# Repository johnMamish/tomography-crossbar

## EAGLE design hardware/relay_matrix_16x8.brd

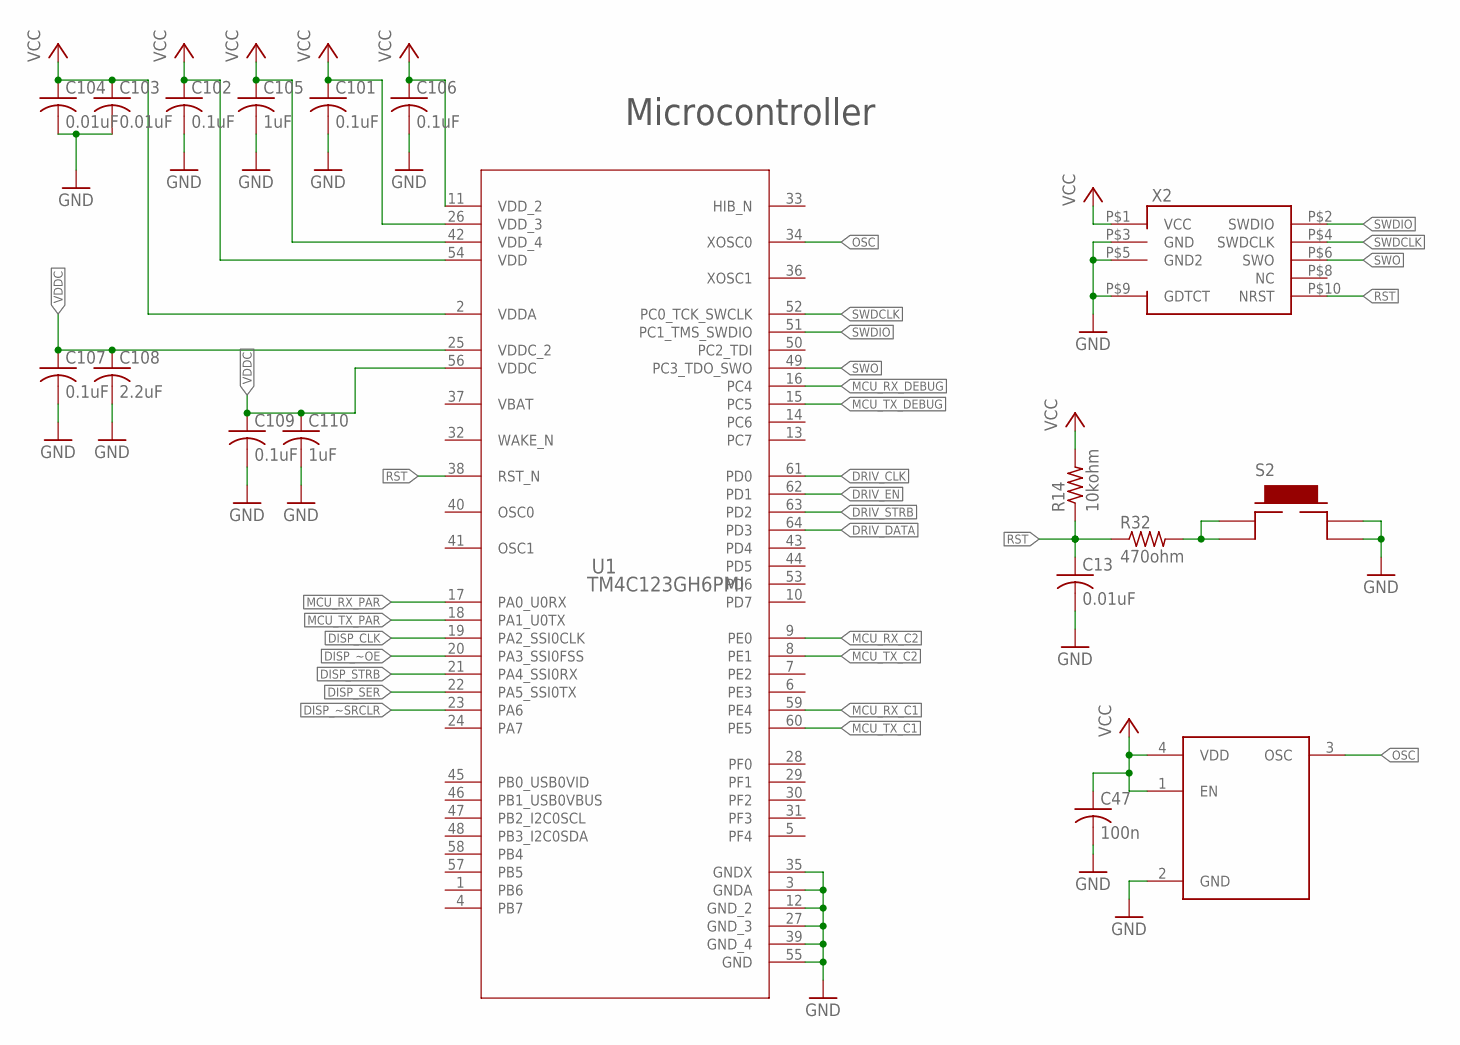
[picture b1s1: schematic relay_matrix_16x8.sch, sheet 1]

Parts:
C13, C103, C104: 0.01uF; C0402; MANUFACTURER_PART_NUMBER GCM155R71H103KA55D
C47: 100n; C0402; MANUFACTURER_PART_NUMBER CL05B104KO5NNNC
C101, C102, C106, C107, C109: 0.1uF; C0402; MANUFACTURER_PART_NUMBER CL05B104KO5NNNC
C105, C110: 1uF; C0402; MANUFACTURER_PART_NUMBER CL05A105KO5NNNC
C108: 2.2uF; C0603; MANUFACTURER_PART_NUMBER CL10A225KO8NNNC
R14: 10kohm; R0402; MANUFACTURER_PART_NUMBER RC1005F103CS
R32: 470ohm; R0402; MANUFACTURER_PART_NUMBER RC0402JR-07470RL
S2: TE_FSM4JSMA; TE_FSMJSMA; MANUFACTURER_PART_NUMBER FSM4JSMA
U1: TM4C123GH6PMI; PM0064A_N
U5: ECS-2033-080-AU; OSCCC250X200X110N; MANUFACTURER_PART_NUMBER ECS-2033-080-AU
X2: FTSH-105-01-F-DV-007-K-P; MANUFACTURER_PART_NUMBER FTSH-105-01-F-DV-007-K-P

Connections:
!RST: C13.1, R14.1, R32.1, U1.38 (RST_N), X2.P$10 (NRST)
DISP_CLK: U1.19 (PA2_SSI0CLK); also elsewhere on the board
DISP_SER: U1.22 (PA5_SSI0TX); also elsewhere on the board
DISP_STRB: U1.21 (PA4_SSI0RX); also elsewhere on the board
DISP_~OE: U1.20 (PA3_SSI0FSS); also elsewhere on the board
DISP_~SRCLR: U1.23 (PA6); also elsewhere on the board
DRIV_CLK: U1.61 (PD0); also elsewhere on the board
DRIV_DATA: U1.64 (PD3); also elsewhere on the board
DRIV_EN: U1.62 (PD1); also elsewhere on the board
DRIV_STRB: U1.63 (PD2); also elsewhere on the board
GND: C13.2, C47.2, C101.2, C102.2, C103.2, C104.2, C105.2, C106.2, C107.2, C108.2, C109.2, C110.2, S2.P$3, S2.P$4, U1.3 (GNDA), U1.12 (GND_2), U1.27 (GND_3), U1.35 (GNDX), U1.39 (GND_4), U1.55 (GND), U5.2 (GND), X2.P$3 (GND), X2.P$5 (GND2), X2.P$9 (GDTCT); also elsewhere on the board
MCU_RX_C1: U1.59 (PE4); also elsewhere on the board
MCU_RX_C2: U1.9 (PE0); also elsewhere on the board
MCU_RX_DEBUG: U1.16 (PC4); also elsewhere on the board
MCU_RX_PAR: U1.17 (PA0_U0RX); also elsewhere on the board
MCU_TX_C1: U1.60 (PE5); also elsewhere on the board
MCU_TX_C2: U1.8 (PE1); also elsewhere on the board
MCU_TX_DEBUG: U1.15 (PC5); also elsewhere on the board
MCU_TX_PAR: U1.18 (PA1_U0TX); also elsewhere on the board
unnamed: R32.2, S2.P$1, S2.P$2
OSC: U1.34 (XOSC0), U5.3 (OSC)
SWDCLK: U1.52 (PC0_TCK_SWCLK), X2.P$4 (SWDCLK)
SWDIO: U1.51 (PC1_TMS_SWDIO), X2.P$2 (SWDIO)
SWO: U1.49 (PC3_TDO_SWO), X2.P$6 (SWO)
VBAT: U1.37 (VBAT)
VCC: C47.1, C101.1, C102.1, C103.1, C104.1, C105.1, C106.1, R14.2, U1.2 (VDDA), U1.11 (VDD_2), U1.26 (VDD_3), U1.42 (VDD_4), U1.54 (VDD), U5.1 (EN), U5.4 (VDD), X2.P$1 (VCC); also elsewhere on the board
VDDC: C107.1, C108.1, C109.1, C110.1, U1.25 (VDDC_2), U1.56 (VDDC)

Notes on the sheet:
Microcontroller

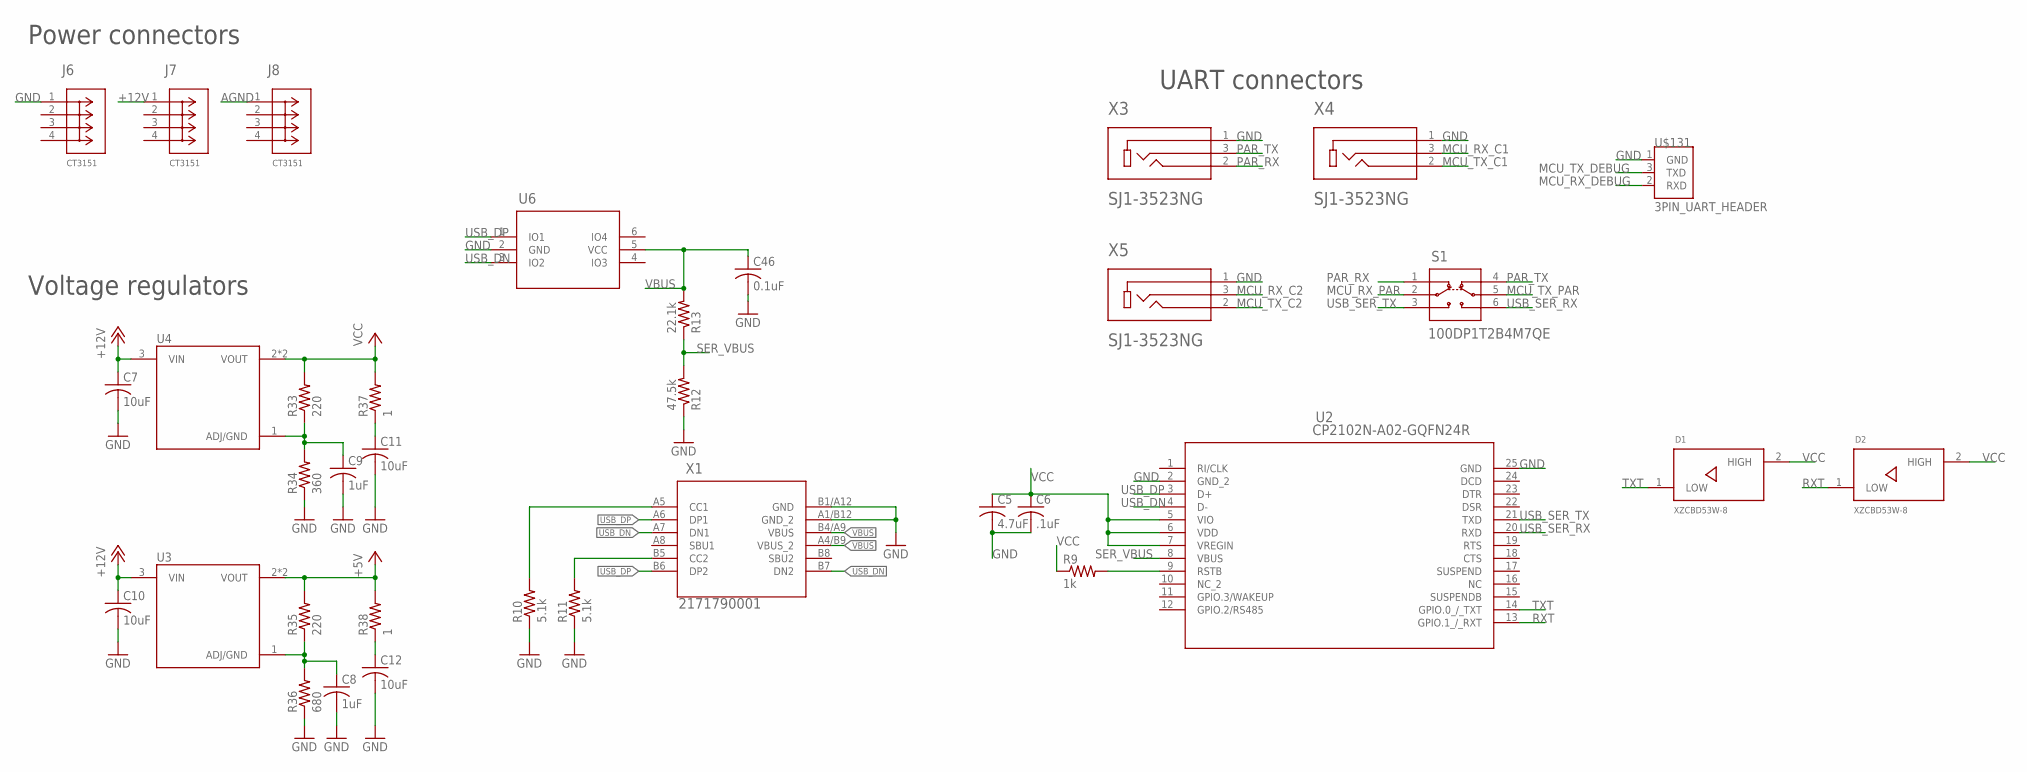
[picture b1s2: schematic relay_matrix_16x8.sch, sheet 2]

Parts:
C5: 4.7uF; C0603; MANUFACTURER_PART_NUMBER CL10A475KA8NQNC
C6: .1uF; C0402; MANUFACTURER_PART_NUMBER CL05A105KO5NNNC
C7, C10, C11, C12: 10uF; C0805; MANUFACTURER_PART_NUMBER CL21A106KAYNNNE
C8, C9: 1uF; C0402; MANUFACTURER_PART_NUMBER CL05A105KO5NNNC
C46: 0.1uF; C0402; MANUFACTURER_PART_NUMBER CL05B104KO5NNNC
D1, D2: XZCBD53W-8; DIOC1608X70N
J6, J7, J8: CT3151; CONN_CT3151
R9: 1k; R0402; MANUFACTURER_PART_NUMBER CRG0402F1K0
R10, R11: 5.1k; R0402; MANUFACTURER_PART_NUMBER RC0402FR-075K1L
R12: 47.5k; R0402; MANUFACTURER_PART_NUMBER RMCF0402FT47K5
R13: 22.1k; R0402; MANUFACTURER_PART_NUMBER RC0402FR-0722K1L
R33, R35: 220; R0603; MANUFACTURER_PART_NUMBER RC1608F221CS
R34: 360; R0603; MANUFACTURER_PART_NUMBER RC0603FR-07360RL
R36: 680; R0603; MANUFACTURER_PART_NUMBER RC0603FR-07680RL
R37, R38: 1; R0603; MANUFACTURER_PART_NUMBER RC0603FR-071RL
S1: 100DP1T2B4M7QE; 100DP1T2B4M7QE_EWI
U2: CP2102N-A02-GQFN24R; QFN24_SIL
U3, U4: NCP1117XXA; TO230P990X240-4N; MANUFACTURER_PART_NUMBER NCP1117IDTAT4G
U6: TPD4E001RDBVR; DBV6
U$131: 3PIN_UART_HEADER; HDRV3W64P254_1X3_1016X277X854B
X1: 2171790001; 2171790001_MOL
X3, X4, X5: SJ1-3523NG; CUI_SJ1-3523NG; MANUFACTURER_PART_NUMBER SJ1-3523NG

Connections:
+5V: R35.2, R38.2, U3.2 (VOUT), U3.4 (VOUT); also elsewhere on the board
+12V: C7.1, C10.1, J7.1, U3.3 (VIN), U4.3 (VIN)
AGND: J8.1; also elsewhere on the board
GND: C5.2, C6.2, C7.2, C8.2, C9.2, C10.2, C11.2, C12.2, C46.2, J6.1, R10.1, R11.1, R12.1, R34.1, R36.1, U2.2 (GND_2), U2.25 (GND), U6.2 (GND), U$131.1 (GND), X1.A1/B12 (GND_2), X1.B1/A12 (GND), X3.1, X4.1, X5.1; also elsewhere on the board
MCU_RX_C1: X4.3; also elsewhere on the board
MCU_RX_C2: X5.3; also elsewhere on the board
MCU_RX_DEBUG: U$131.2 (RXD); also elsewhere on the board
MCU_RX_PAR: S1.2; also elsewhere on the board
MCU_TX_C1: X4.2; also elsewhere on the board
MCU_TX_C2: X5.2; also elsewhere on the board
MCU_TX_DEBUG: U$131.3 (TXD); also elsewhere on the board
MCU_TX_PAR: S1.5; also elsewhere on the board
unnamed: R9.2, U2.9 (RSTB)
unnamed: R10.2, X1.A5 (CC1)
unnamed: R11.2, X1.B5 (CC2)
unnamed: C9.1, R33.1, R34.2, U4.1 (ADJ/GND)
unnamed: C8.1, R35.1, R36.2, U3.1 (ADJ/GND)
unnamed: C11.1, R37.1
unnamed: C12.1, R38.1
PAR_RX: S1.1, X3.2
PAR_TX: S1.4, X3.3
RXT: D2.1 (LOW), U2.13 (GPIO.1_/_RXT)
SER_VBUS: R12.2, R13.1, U2.8 (VBUS)
TXT: D1.1 (LOW), U2.14 (GPIO.0_/_TXT)
USB_DN: U2.4 (D-), U6.3 (IO2), X1.A7 (DN1), X1.B7 (DN2)
USB_DP: U2.3 (D+), U6.1 (IO1), X1.A6 (DP1), X1.B6 (DP2)
USB_SER_RX: S1.6, U2.20 (RXD)
USB_SER_TX: S1.3, U2.21 (TXD)
VBUS: C46.1, R13.2, U6.5 (VCC), X1.A4/B9 (VBUS_2), X1.B4/A9 (VBUS)
VCC: C5.1, C6.1, D1.2 (HIGH), D2.2 (HIGH), R9.1, R33.2, R37.2, U2.5 (VIO), U2.6 (VDD), U2.7 (VREGIN), U4.2 (VOUT), U4.4 (VOUT); also elsewhere on the board

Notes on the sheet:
UART connectors
Power connectors
Voltage regulators

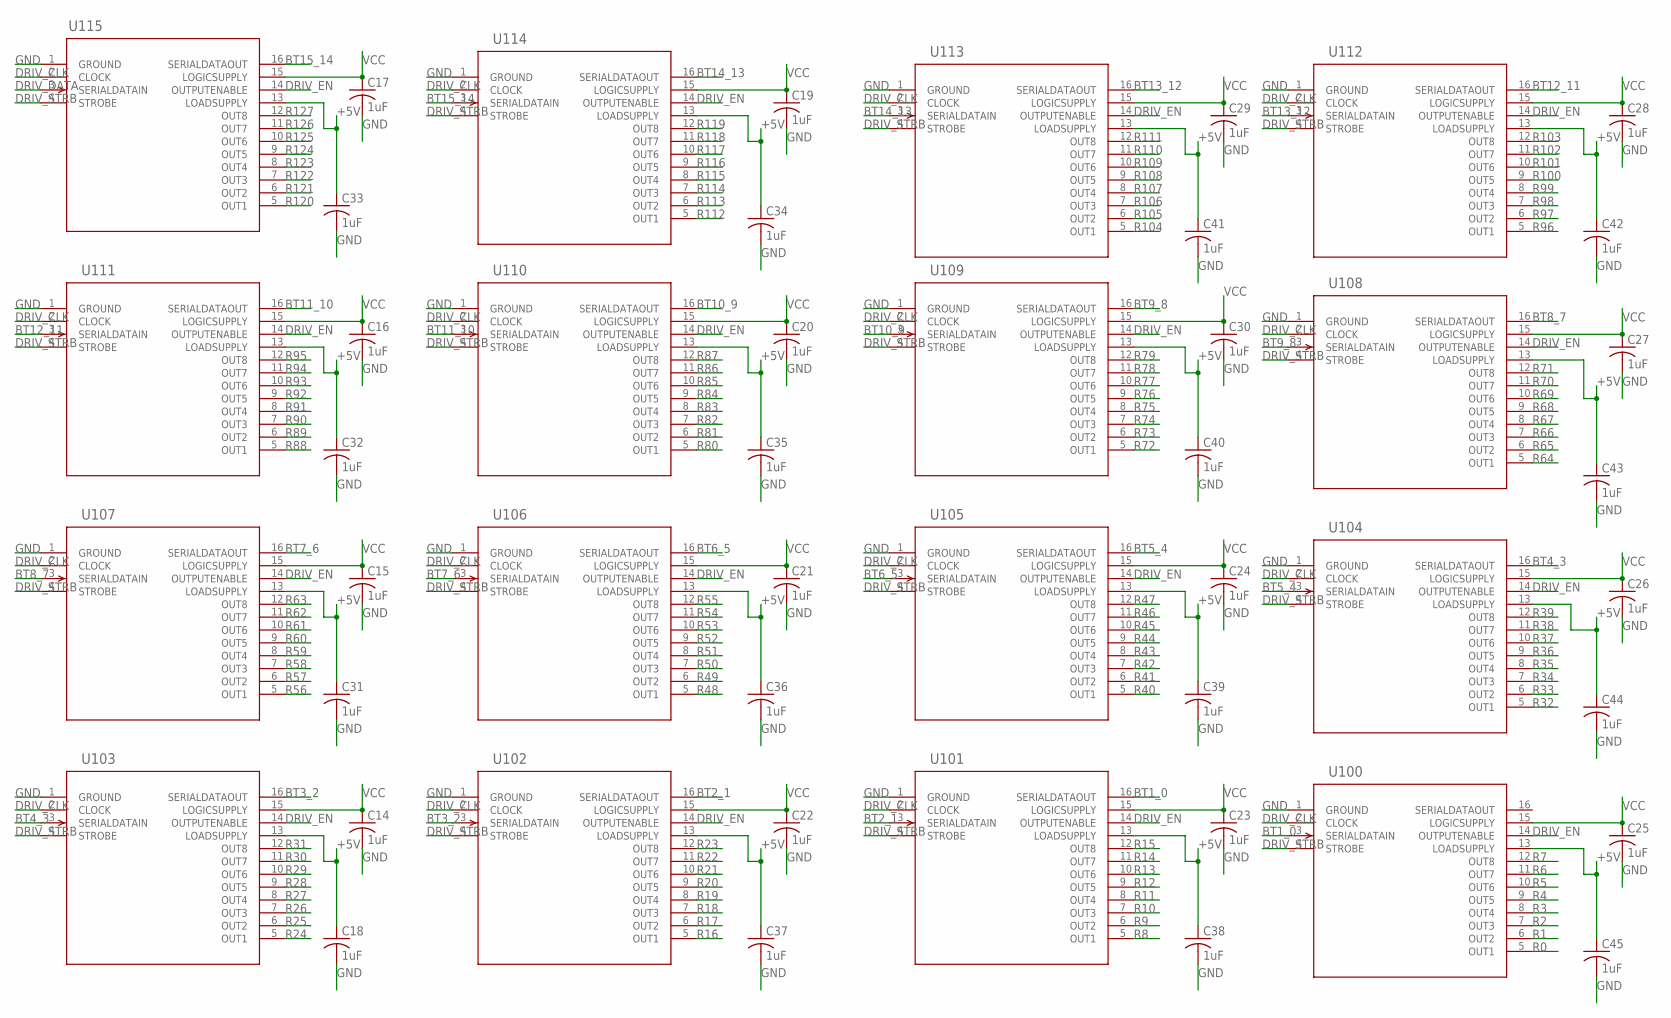
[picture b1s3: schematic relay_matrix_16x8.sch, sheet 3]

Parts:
C14, C15, C16, C17, C18, C19, C20, C21, C22, C23, C24, C25, C26, C27, C28, C29, C30, C31, C32, C33, C34, C35, C36, C37, C38, C39, C40, C41, C42, C43, C44, C45: 1uF; C0402; MANUFACTURER_PART_NUMBER CL05A105KO5NNNC
U100, U101, U102, U103, U104, U105, U106, U107, U108, U109, U110, U111, U112, U113, U114, U115: MIC5891YWM-TR; SOIC-16_WM_MCH

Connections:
+5V: C18.1, C31.1, C32.1, C33.1, C34.1, C35.1, C36.1, C37.1, C38.1, C39.1, C40.1, C41.1, C42.1, C43.1, C44.1, C45.1, U100.13 (LOADSUPPLY), U101.13 (LOADSUPPLY), U102.13 (LOADSUPPLY), U103.13 (LOADSUPPLY), U104.13 (LOADSUPPLY), U105.13 (LOADSUPPLY), U106.13 (LOADSUPPLY), U107.13 (LOADSUPPLY), U108.13 (LOADSUPPLY), U109.13 (LOADSUPPLY), U110.13 (LOADSUPPLY), U111.13 (LOADSUPPLY), U112.13 (LOADSUPPLY), U113.13 (LOADSUPPLY), U114.13 (LOADSUPPLY), U115.13 (LOADSUPPLY); also elsewhere on the board
BT1_0: U100.3 (SERIALDATAIN), U101.16 (SERIALDATAOUT)
BT2_1: U101.3 (SERIALDATAIN), U102.16 (SERIALDATAOUT)
BT3_2: U102.3 (SERIALDATAIN), U103.16 (SERIALDATAOUT)
BT4_3: U103.3 (SERIALDATAIN), U104.16 (SERIALDATAOUT)
BT5_4: U104.3 (SERIALDATAIN), U105.16 (SERIALDATAOUT)
BT6_5: U105.3 (SERIALDATAIN), U106.16 (SERIALDATAOUT)
BT7_6: U106.3 (SERIALDATAIN), U107.16 (SERIALDATAOUT)
BT8_7: U107.3 (SERIALDATAIN), U108.16 (SERIALDATAOUT)
BT9_8: U108.3 (SERIALDATAIN), U109.16 (SERIALDATAOUT)
BT10_9: U109.3 (SERIALDATAIN), U110.16 (SERIALDATAOUT)
BT11_10: U110.3 (SERIALDATAIN), U111.16 (SERIALDATAOUT)
BT12_11: U111.3 (SERIALDATAIN), U112.16 (SERIALDATAOUT)
BT13_12: U112.3 (SERIALDATAIN), U113.16 (SERIALDATAOUT)
BT14_13: U113.3 (SERIALDATAIN), U114.16 (SERIALDATAOUT)
BT15_14: U114.3 (SERIALDATAIN), U115.16 (SERIALDATAOUT)
DRIV_CLK: U100.2 (CLOCK), U101.2 (CLOCK), U102.2 (CLOCK), U103.2 (CLOCK), U104.2 (CLOCK), U105.2 (CLOCK), U106.2 (CLOCK), U107.2 (CLOCK), U108.2 (CLOCK), U109.2 (CLOCK), U110.2 (CLOCK), U111.2 (CLOCK), U112.2 (CLOCK), U113.2 (CLOCK), U114.2 (CLOCK), U115.2 (CLOCK); also elsewhere on the board
DRIV_DATA: U115.3 (SERIALDATAIN); also elsewhere on the board
DRIV_EN: U100.14 (OUTPUTENABLE), U101.14 (OUTPUTENABLE), U102.14 (OUTPUTENABLE), U103.14 (OUTPUTENABLE), U104.14 (OUTPUTENABLE), U105.14 (OUTPUTENABLE), U106.14 (OUTPUTENABLE), U107.14 (OUTPUTENABLE), U108.14 (OUTPUTENABLE), U109.14 (OUTPUTENABLE), U110.14 (OUTPUTENABLE), U111.14 (OUTPUTENABLE), U112.14 (OUTPUTENABLE), U113.14 (OUTPUTENABLE), U114.14 (OUTPUTENABLE), U115.14 (OUTPUTENABLE); also elsewhere on the board
DRIV_STRB: U100.4 (STROBE), U101.4 (STROBE), U102.4 (STROBE), U103.4 (STROBE), U104.4 (STROBE), U105.4 (STROBE), U106.4 (STROBE), U107.4 (STROBE), U108.4 (STROBE), U109.4 (STROBE), U110.4 (STROBE), U111.4 (STROBE), U112.4 (STROBE), U113.4 (STROBE), U114.4 (STROBE), U115.4 (STROBE); also elsewhere on the board
GND: C14.2, C15.2, C16.2, C17.2, C18.2, C19.2, C20.2, C21.2, C22.2, C23.2, C24.2, C25.2, C26.2, C27.2, C28.2, C29.2, C30.2, C31.2, C32.2, C33.2, C34.2, C35.2, C36.2, C37.2, C38.2, C39.2, C40.2, C41.2, C42.2, C43.2, C44.2, C45.2, U100.1 (GROUND), U101.1 (GROUND), U102.1 (GROUND), U103.1 (GROUND), U104.1 (GROUND), U105.1 (GROUND), U106.1 (GROUND), U107.1 (GROUND), U108.1 (GROUND), U109.1 (GROUND), U110.1 (GROUND), U111.1 (GROUND), U112.1 (GROUND), U113.1 (GROUND), U114.1 (GROUND), U115.1 (GROUND); also elsewhere on the board
R0: U100.5 (OUT1); also elsewhere on the board
R1: U100.6 (OUT2); also elsewhere on the board
R2: U100.7 (OUT3); also elsewhere on the board
R3: U100.8 (OUT4); also elsewhere on the board
R4: U100.9 (OUT5); also elsewhere on the board
R5: U100.10 (OUT6); also elsewhere on the board
R6: U100.11 (OUT7); also elsewhere on the board
R7: U100.12 (OUT8); also elsewhere on the board
R8: U101.5 (OUT1); also elsewhere on the board
R9: U101.6 (OUT2); also elsewhere on the board
R10: U101.7 (OUT3); also elsewhere on the board
R11: U101.8 (OUT4); also elsewhere on the board
R12: U101.9 (OUT5); also elsewhere on the board
R13: U101.10 (OUT6); also elsewhere on the board
R14: U101.11 (OUT7); also elsewhere on the board
R15: U101.12 (OUT8); also elsewhere on the board
R16: U102.5 (OUT1); also elsewhere on the board
R17: U102.6 (OUT2); also elsewhere on the board
R18: U102.7 (OUT3); also elsewhere on the board
R19: U102.8 (OUT4); also elsewhere on the board
R20: U102.9 (OUT5); also elsewhere on the board
R21: U102.10 (OUT6); also elsewhere on the board
R22: U102.11 (OUT7); also elsewhere on the board
R23: U102.12 (OUT8); also elsewhere on the board
R24: U103.5 (OUT1); also elsewhere on the board
R25: U103.6 (OUT2); also elsewhere on the board
R26: U103.7 (OUT3); also elsewhere on the board
R27: U103.8 (OUT4); also elsewhere on the board
R28: U103.9 (OUT5); also elsewhere on the board
R29: U103.10 (OUT6); also elsewhere on the board
R30: U103.11 (OUT7); also elsewhere on the board
R31: U103.12 (OUT8); also elsewhere on the board
R32: U104.5 (OUT1); also elsewhere on the board
R33: U104.6 (OUT2); also elsewhere on the board
R34: U104.7 (OUT3); also elsewhere on the board
R35: U104.8 (OUT4); also elsewhere on the board
R36: U104.9 (OUT5); also elsewhere on the board
R37: U104.10 (OUT6); also elsewhere on the board
R38: U104.11 (OUT7); also elsewhere on the board
R39: U104.12 (OUT8); also elsewhere on the board
R40: U105.5 (OUT1); also elsewhere on the board
R41: U105.6 (OUT2); also elsewhere on the board
R42: U105.7 (OUT3); also elsewhere on the board
R43: U105.8 (OUT4); also elsewhere on the board
R44: U105.9 (OUT5); also elsewhere on the board
R45: U105.10 (OUT6); also elsewhere on the board
R46: U105.11 (OUT7); also elsewhere on the board
R47: U105.12 (OUT8); also elsewhere on the board
R48: U106.5 (OUT1); also elsewhere on the board
R49: U106.6 (OUT2); also elsewhere on the board
R50: U106.7 (OUT3); also elsewhere on the board
R51: U106.8 (OUT4); also elsewhere on the board
R52: U106.9 (OUT5); also elsewhere on the board
R53: U106.10 (OUT6); also elsewhere on the board
R54: U106.11 (OUT7); also elsewhere on the board
R55: U106.12 (OUT8); also elsewhere on the board
R56: U107.5 (OUT1); also elsewhere on the board
R57: U107.6 (OUT2); also elsewhere on the board
R58: U107.7 (OUT3); also elsewhere on the board
R59: U107.8 (OUT4); also elsewhere on the board
R60: U107.9 (OUT5); also elsewhere on the board
R61: U107.10 (OUT6); also elsewhere on the board
R62: U107.11 (OUT7); also elsewhere on the board
R63: U107.12 (OUT8); also elsewhere on the board
R64: U108.5 (OUT1); also elsewhere on the board
R65: U108.6 (OUT2); also elsewhere on the board
R66: U108.7 (OUT3); also elsewhere on the board
R67: U108.8 (OUT4); also elsewhere on the board
R68: U108.9 (OUT5); also elsewhere on the board
R69: U108.10 (OUT6); also elsewhere on the board
R70: U108.11 (OUT7); also elsewhere on the board
R71: U108.12 (OUT8); also elsewhere on the board
R72: U109.5 (OUT1); also elsewhere on the board
R73: U109.6 (OUT2); also elsewhere on the board
R74: U109.7 (OUT3); also elsewhere on the board
R75: U109.8 (OUT4); also elsewhere on the board
R76: U109.9 (OUT5); also elsewhere on the board
R77: U109.10 (OUT6); also elsewhere on the board
R78: U109.11 (OUT7); also elsewhere on the board
R79: U109.12 (OUT8); also elsewhere on the board
R80: U110.5 (OUT1); also elsewhere on the board
R81: U110.6 (OUT2); also elsewhere on the board
R82: U110.7 (OUT3); also elsewhere on the board
R83: U110.8 (OUT4); also elsewhere on the board
R84: U110.9 (OUT5); also elsewhere on the board
R85: U110.10 (OUT6); also elsewhere on the board
R86: U110.11 (OUT7); also elsewhere on the board
R87: U110.12 (OUT8); also elsewhere on the board
R88: U111.5 (OUT1); also elsewhere on the board
R89: U111.6 (OUT2); also elsewhere on the board
R90: U111.7 (OUT3); also elsewhere on the board
R91: U111.8 (OUT4); also elsewhere on the board
R92: U111.9 (OUT5); also elsewhere on the board
R93: U111.10 (OUT6); also elsewhere on the board
R94: U111.11 (OUT7); also elsewhere on the board
R95: U111.12 (OUT8); also elsewhere on the board
R96: U112.5 (OUT1); also elsewhere on the board
R97: U112.6 (OUT2); also elsewhere on the board
R98: U112.7 (OUT3); also elsewhere on the board
R99: U112.8 (OUT4); also elsewhere on the board
R100: U112.9 (OUT5); also elsewhere on the board
R101: U112.10 (OUT6); also elsewhere on the board
R102: U112.11 (OUT7); also elsewhere on the board
R103: U112.12 (OUT8); also elsewhere on the board
R104: U113.5 (OUT1); also elsewhere on the board
R105: U113.6 (OUT2); also elsewhere on the board
R106: U113.7 (OUT3); also elsewhere on the board
R107: U113.8 (OUT4); also elsewhere on the board
R108: U113.9 (OUT5); also elsewhere on the board
R109: U113.10 (OUT6); also elsewhere on the board
R110: U113.11 (OUT7); also elsewhere on the board
R111: U113.12 (OUT8); also elsewhere on the board
R112: U114.5 (OUT1); also elsewhere on the board
R113: U114.6 (OUT2); also elsewhere on the board
R114: U114.7 (OUT3); also elsewhere on the board
R115: U114.8 (OUT4); also elsewhere on the board
R116: U114.9 (OUT5); also elsewhere on the board
R117: U114.10 (OUT6); also elsewhere on the board
R118: U114.11 (OUT7); also elsewhere on the board
R119: U114.12 (OUT8); also elsewhere on the board
R120: U115.5 (OUT1); also elsewhere on the board
R121: U115.6 (OUT2); also elsewhere on the board
R122: U115.7 (OUT3); also elsewhere on the board
R123: U115.8 (OUT4); also elsewhere on the board
R124: U115.9 (OUT5); also elsewhere on the board
R125: U115.10 (OUT6); also elsewhere on the board
R126: U115.11 (OUT7); also elsewhere on the board
R127: U115.12 (OUT8); also elsewhere on the board
VCC: C14.1, C15.1, C16.1, C17.1, C19.1, C20.1, C21.1, C22.1, C23.1, C24.1, C25.1, C26.1, C27.1, C28.1, C29.1, C30.1, U100.15 (LOGICSUPPLY), U101.15 (LOGICSUPPLY), U102.15 (LOGICSUPPLY), U103.15 (LOGICSUPPLY), U104.15 (LOGICSUPPLY), U105.15 (LOGICSUPPLY), U106.15 (LOGICSUPPLY), U107.15 (LOGICSUPPLY), U108.15 (LOGICSUPPLY), U109.15 (LOGICSUPPLY), U110.15 (LOGICSUPPLY), U111.15 (LOGICSUPPLY), U112.15 (LOGICSUPPLY), U113.15 (LOGICSUPPLY), U114.15 (LOGICSUPPLY), U115.15 (LOGICSUPPLY); also elsewhere on the board

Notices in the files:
parts and their libraries:
COPYRIGHT: Copyright (C) 2021 Ultra Librarian. All rights reserved.
